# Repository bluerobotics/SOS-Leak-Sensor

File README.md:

# SOS-Leak-Sensor

Simple water leak sensor for ROVs and AUVs. 

For more information, please see the [main documentation](http://docs.bluerobotics.com/sos/)

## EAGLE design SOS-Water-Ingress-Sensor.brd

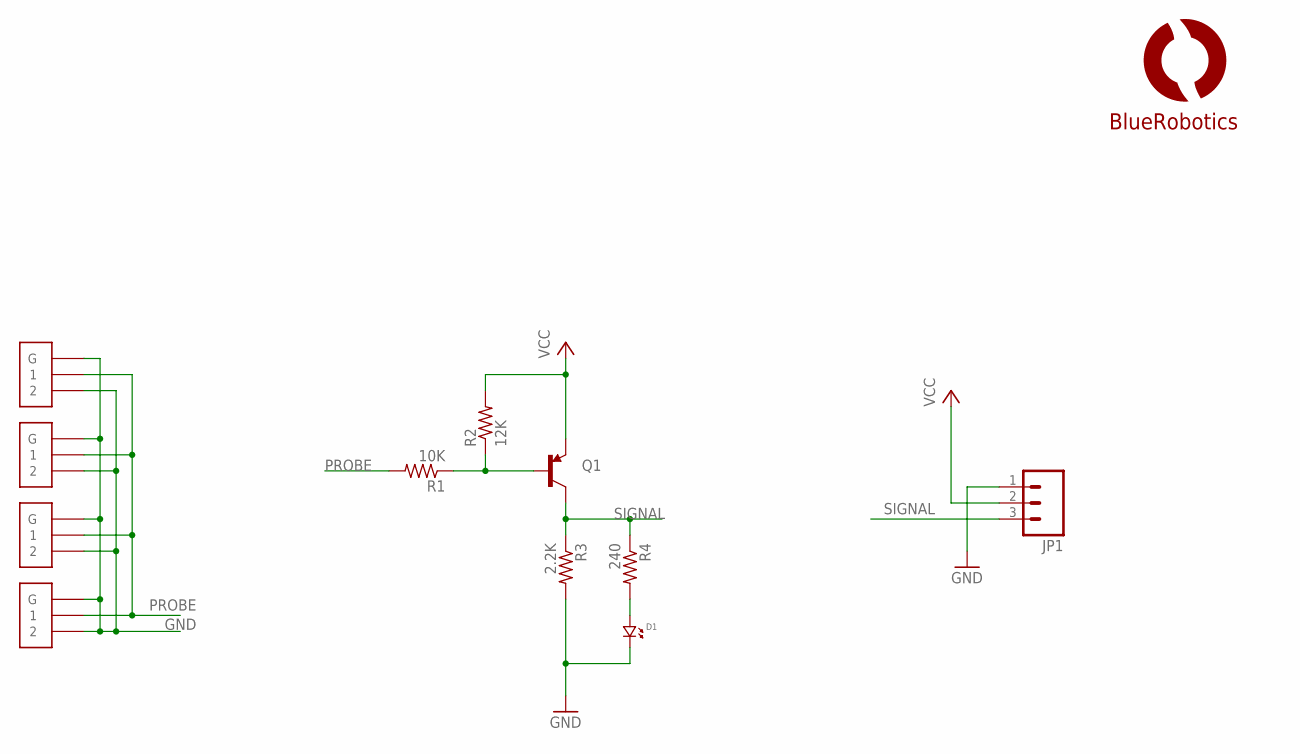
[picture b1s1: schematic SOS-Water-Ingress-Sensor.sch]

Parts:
D1: LED.0805; 0805.LED
JP1: M03PTH; 1X03
Q1: TRANSISTOR_PNPSMD; SOT23-3
R1: 10K; R0603
R2: 12K; R0603
R3: 2.2K; R0603
R4: 240; R0603
U$1, U$2, U$3, U$4: JSH-GH-2VERT; JST-GH-TOP-2
U$7: LOGOBR-LOGO-S; BR-LOGO-SMALL

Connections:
GND: D1.P$2 (2), JP1.1, R3.2, U$1.2, U$1.MECH1 (G), U$1.MECH2 (G), U$2.2, U$2.MECH1 (G), U$2.MECH2 (G), U$3.2, U$3.MECH1 (G), U$3.MECH2 (G), U$4.2, U$4.MECH1 (G), U$4.MECH2 (G)
unnamed: Q1.1 (B), R1.1, R2.1
unnamed: D1.P$1 (1), R4.2
PROBE: R1.2, U$1.1, U$2.1, U$3.1, U$4.1
SIGNAL: JP1.3, Q1.3 (C), R3.1, R4.1
VCC: JP1.2, Q1.2 (E), R2.2

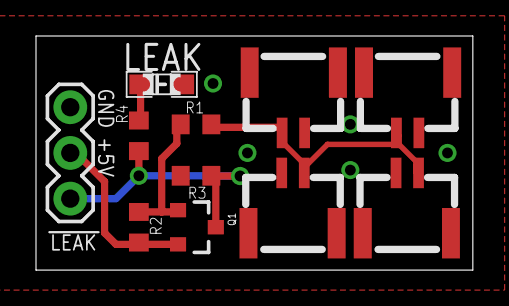
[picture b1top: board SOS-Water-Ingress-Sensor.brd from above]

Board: 2 copper layers, 24.3 x 13.0 mm, 12 parts (1 on the bottom side), 6 nets.

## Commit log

2016-02-09 Added starting sch and brd files.
2016-08-23 Update board design and schematic.
2016-08-25 Added LED indicator and resistor, completed board layout.
2016-08-26 Update silkscreen and layout.
2016-08-26 Widened board slightly and fixed all clearance errors.
2016-08-26 Minor tweaks to layout all around.
2016-09-26 Updated pull-down resistor to 2.2k.
2016-10-04 Change component values and layout.
2016-11-16 Rename files.
2016-11-16 Update readme.
2016-11-16 Added PDF
2019-08-28 Add Arduino example sketch from Nick N

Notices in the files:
parts and their libraries:
SparkFun-DiscreteSemi: Licensing: Creative Commons ShareAlike 4.0 International - https://creativecommons.org/licenses/by-sa/4.0
